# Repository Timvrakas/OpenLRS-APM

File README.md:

OpenLRS-APM
===========

A set of OpenLRS Radio Hardware designed for use with the APM/Pixhawk project

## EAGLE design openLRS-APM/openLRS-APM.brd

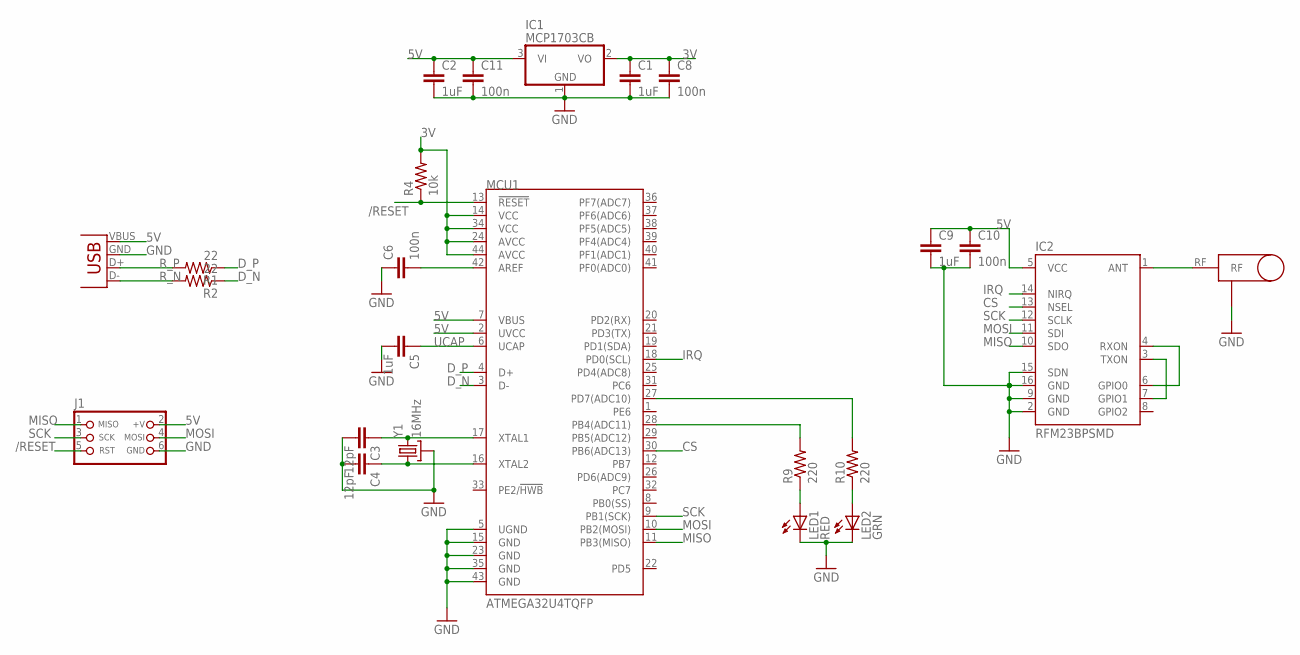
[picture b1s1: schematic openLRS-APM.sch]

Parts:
C1, C2, C5, C9: 1uF; 0805
C3, C4: 12pF; 0805
C6, C8, C10, C11: 100n; 0805
IC1: MCP1703CB; SOT23
IC2: RFM23BPSMD; RFM23BP-S2
J1: CON_HEADER_PRG_AVR_ICSP-SMD; M2X3_SMD
JP1: USB-A-H
LED1: RED; SML0805
LED2: GRN; SML0805
MCU1: ATMEGA32U4TQFP; SPARKFUN-DIGITALIC_TQFP44
R1, R2: 22; 0805
R4: 10k; 0805
R9, R10: 220; 0805
U$4: LINX-SMA
Y1: 16MHz; CRYSTAL-SMD-5X3

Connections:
3V: C1.1, C8.1, IC1.2 (VO), MCU1.14 (VCC), MCU1.24 (AVCC), MCU1.34 (VCC), MCU1.44 (AVCC), R4.2
5V: C2.1, C9.1, C10.1, C11.1, IC1.3 (VI), IC2.5 (VCC), J1.2 (+V), JP1.VBUS (GND), MCU1.2 (UVCC), MCU1.7 (VBUS)
/RESET: J1.5 (RST), MCU1.13 (!RESET), R4.1
CS: IC2.13 (NSEL), MCU1.30 (PB6(ADC13))
D_N: MCU1.3 (D-), R2.1
D_P: MCU1.4 (D+), R1.1
GND: C1.2, C2.2, C3.2, C4.2, C5.2, C6.1, C8.2, C9.2, C10.2, C11.2, IC1.1 (GND), IC2.2 (GND), IC2.9 (GND), IC2.15 (SDN), IC2.16 (GND), J1.6 (GND), JP1.GND (VBUS), LED1.C, LED2.C, MCU1.5 (UGND), MCU1.15 (GND), MCU1.23 (GND), MCU1.35 (GND), MCU1.43 (GND), U$4.GND1 (GND), U$4.GND2 (GND), U$4.GND3 (GND), U$4.GND4 (GND), Y1.2 (GND), Y1.4 (GND)
IRQ: IC2.14 (NIRQ), MCU1.18 (PD0(SCL))
MISO: IC2.10 (SDO), J1.1 (MISO), MCU1.11 (PB3(MISO))
MOSI: IC2.11 (SDI), J1.4 (MOSI), MCU1.10 (PB2(MOSI))
unnamed: IC2.3 (TXON), IC2.7 (GPIO1)
unnamed: IC2.4 (RXON), IC2.6 (GPIO0)
unnamed: C6.2, MCU1.42 (AREF)
unnamed: MCU1.28 (PB4(ADC11)), R9.2
unnamed: MCU1.27 (PD7(ADC10)), R10.2
unnamed: LED2.A, R10.1
unnamed: LED1.A, R9.1
unnamed: C3.1, MCU1.17 (XTAL1), Y1.3 (2)
unnamed: C4.1, MCU1.16 (XTAL2), Y1.1
unnamed: IC2.1 (ANT), U$4.RF
R_N: JP1.D- (D+), R2.2
R_P: JP1.D+ (D-), R1.2
SCK: IC2.12 (SCLK), J1.3 (SCK), MCU1.9 (PB1(SCK))
UCAP: C5.1, MCU1.6 (UCAP)

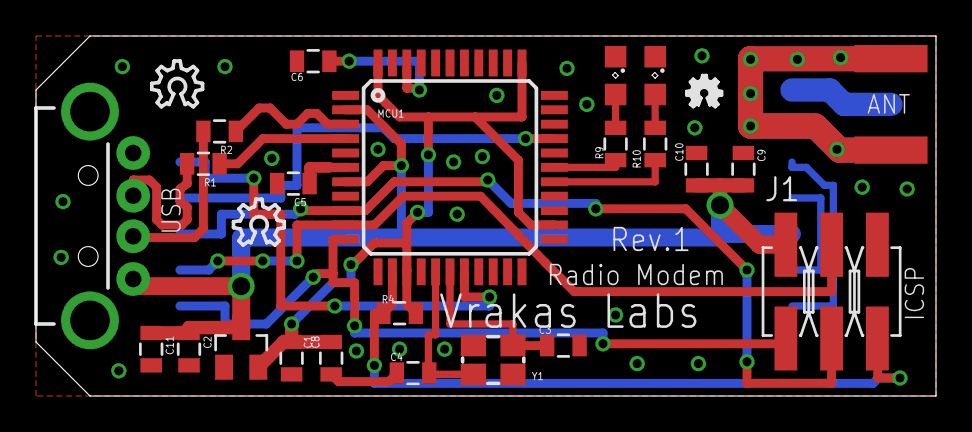
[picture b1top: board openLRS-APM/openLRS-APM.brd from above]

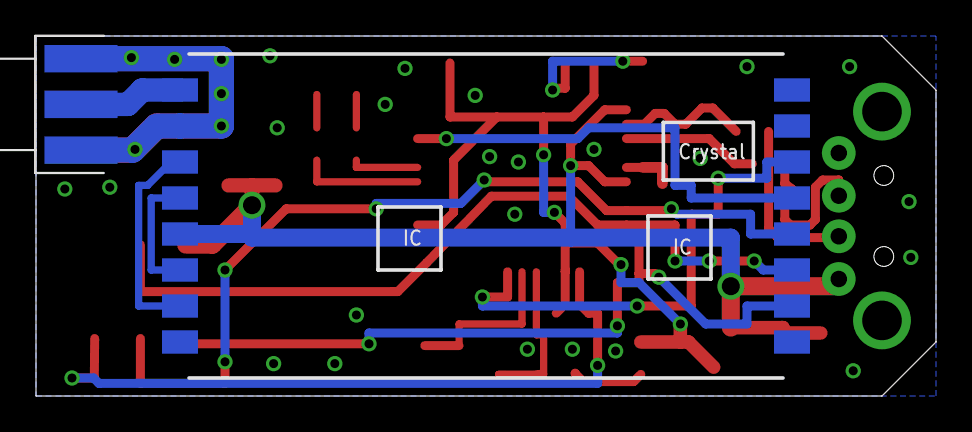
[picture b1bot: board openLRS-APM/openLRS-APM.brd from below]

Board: 2 copper layers, 50.0 x 20.0 mm, 27 parts (2 on the bottom side), 24 nets.

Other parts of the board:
U$1: OSHW_FILLX70_NOTEXT
U$2, U$3: OSHW_8X100_NOTEXT

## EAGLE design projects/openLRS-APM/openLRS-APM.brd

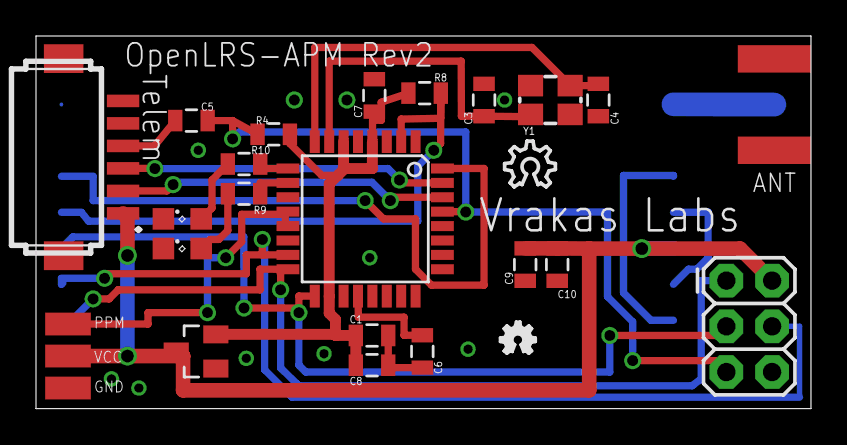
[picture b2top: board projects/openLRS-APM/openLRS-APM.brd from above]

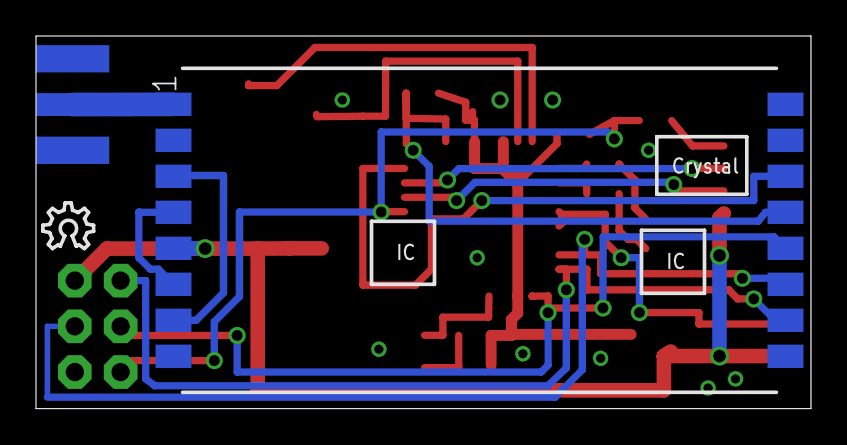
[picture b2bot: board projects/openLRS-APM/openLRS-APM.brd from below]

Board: 2 copper layers, 43.1 x 20.7 mm, 28 parts (3 on the bottom side), 23 nets.

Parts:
C1, C9: 1uF; 0805
C3, C4: 12pF; 0805
C5, C6, C7, C8, C10: 100n; 0805
GND: SMD1,27-2,54
IC1: MCP1703CB; SOT23
IC2: RFM23BPSMD; RFM23BP-S2
J1: AVR_SPI_PRG_6PTH; 2X3
LED1: RED; SML0805
LED2: GRN; SML0805
PPM: SMD1,27-2,54
R4: 10k; 0805
R8: 1k; 0805
R9, R10: 220; 0805
SMA: SMA_EDGELAUNCH
TELEMETRY: DF13-6P-1.25H; DF13A-6P-1.25H
U1: ATMEGA328P; TQFP32-08
U$1: OSHW_FILLX70_NOTEXT
U$2, U$3: OSHW_8X100_NOTEXT
VCC: SMD1,27-2,54
Y1: 16MHz; CRYSTAL-SMD-5X3

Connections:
3V: C1.1, C7.1, C8.1, IC1.2, R4.2, R8.2, U1.4, U1.6, U1.18
5V: C9.1, C10.1, IC1.3, IC2.5, J1.2, TELEMETRY.P$1, VCC.1
/RESET: C5.2, J1.5, R4.1, U1.29
DTR: C5.1, TELEMETRY.P$4
GND: C1.2, C3.2, C4.2, C6.1, C7.2, C8.2, C9.2, C10.2, GND.1, IC1.1, IC2.2, IC2.9, IC2.15, IC2.16, J1.6, LED1.C, LED2.C, SMA.GND@1, SMA.GND@2, SMA.GND@3, SMA.GND@4, TELEMETRY.P$5, TELEMETRY.P$6, U1.3, U1.5, U1.21, Y1.2, Y1.4
MISO: IC2.10, J1.1, U1.16
MOSI: IC2.11, J1.4, U1.15
unnamed: IC2.3, IC2.7
unnamed: IC2.4, IC2.6
unnamed: R9.2, U1.10
unnamed: R10.2, U1.9
unnamed: LED2.A, R10.1
unnamed: LED1.A, R9.1
unnamed: C3.1, U1.7, Y1.3
unnamed: C4.1, U1.8, Y1.1
unnamed: IC2.1, SMA.P
unnamed: C6.2, U1.20
PPM: PPM.1, U1.12, U1.13
RF_CS: IC2.13, R8.1, U1.2
RF_IRQ: IC2.14, U1.32
RXD: TELEMETRY.P$2, U1.30
SCK: IC2.12, J1.3, U1.17
TXD: TELEMETRY.P$3, U1.31

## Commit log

2014-06-17 Migration To GitHub
    Added all previous files. Suspect some libraries are unused.
2014-06-17 Fixed designs
    Ready for first fabrication (I hope). Cleaned and prepared.
2014-06-17 Cleaned, Checked, fixed Ground planes
    Beefed up Power busses. Fixed the Telemetry Pinout.
    Closer to a polished Revision one. Will look into DF-13 PPM signals.
2014-06-18 Changed LED's to 0805.
    Prototype Soon. all SMDs are 0805. Hope to find SMA connector
2014-06-18 Hopefully Final Revision
    Added Documentation and replaced SMA with adafruit SMA. Board shrunk,
    and OSH logos added. ready for production. (I HOPE)
2014-06-18 Final Commit before Rev.1 Fab
    Added Logos, Edited designs, Fixed Text
2014-06-20 Change PPM pin to Timer output.
    needed for generating a PPM signal
2014-06-20 PPM feedback is cool too!
    a few things that we need for rev2. the ppm output should be sampled by
    the ICP input.
2014-07-07 Revert 0493923..5027763
    This rolls back to commit 049392304cea7ab2cd1e886349edb191a1876f4a.
2014-07-07 Revert "Revert 0493923..5027763"
    This reverts commit fac72980201380e8e908eea0726af7188bf0a585.
2014-08-27 added 3.3v regulator
    needed for proper voltages to Atmega.
2014-08-27 Mac Folder Troubles!?
2014-08-27 More Troubles?!
2014-08-30 Initial Rev2 Commit
    Rearranged for shrink wrapping, fixed voltage levels. may need routing
    touch up.
2015-02-28 Initial 32u4 USB dongle version
2015-02-28 Reorganized to better integrate with eagle
    also added default .gitignore
2015-02-28 Reorganize for Eagle
    also added .gitignore
2015-03-17 Production Rev.1, changed the SMA connector.

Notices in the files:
parts and their libraries:
SparkFun-DigitalIC: Licensing: CC v3.0 Share-Alike You are welcome to use this library for commercial purposes.
